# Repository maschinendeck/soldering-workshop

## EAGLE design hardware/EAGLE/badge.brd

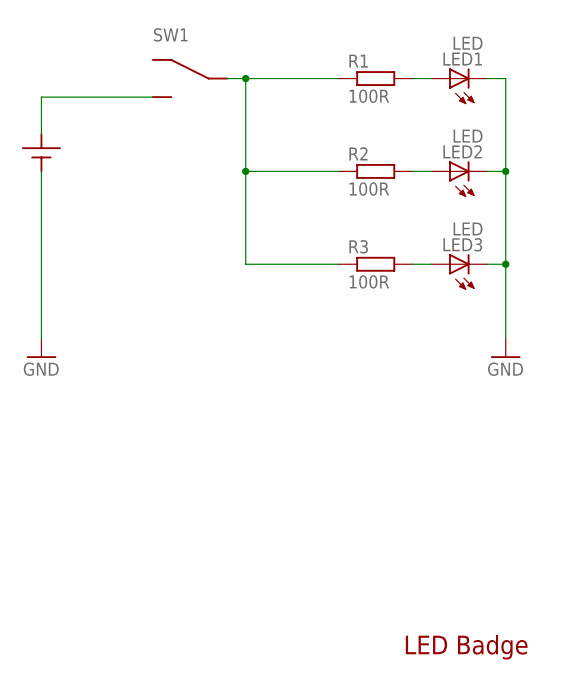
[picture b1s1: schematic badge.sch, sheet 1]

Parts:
LED1, LED2, LED3: LED; LED5MM
R1, R2, R3: 100R; 0207/10
SW1: SWITCH
X1: BATTERYHOLDER_SMD

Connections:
GND: LED1.K (C), LED2.K (C), LED3.K (C), X1.-
unnamed: LED1.A, R1.2
unnamed: R1.1, R2.1, R3.1, SW1.C
unnamed: LED2.A, R2.2
unnamed: LED3.A, R3.2
unnamed: SW1.NO, X1.+

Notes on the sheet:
LED Badge

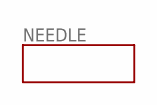
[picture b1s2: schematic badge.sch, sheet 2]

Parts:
NEEDLE: NEEDLE; NEEDLE_PAD

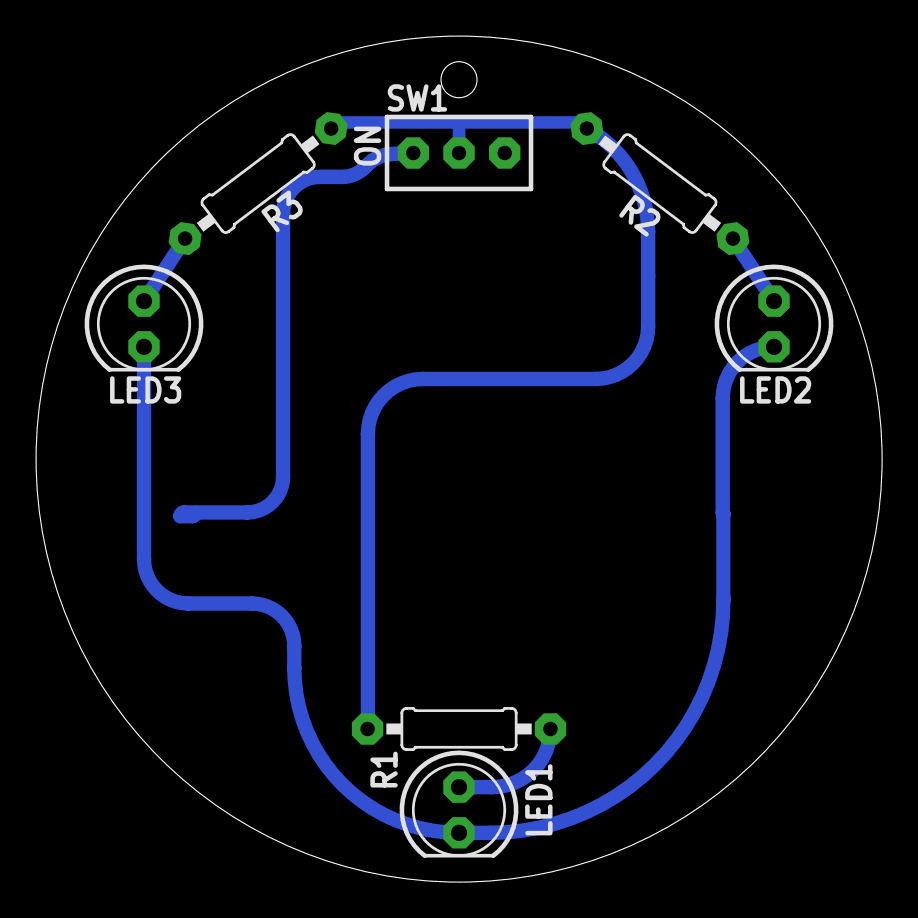
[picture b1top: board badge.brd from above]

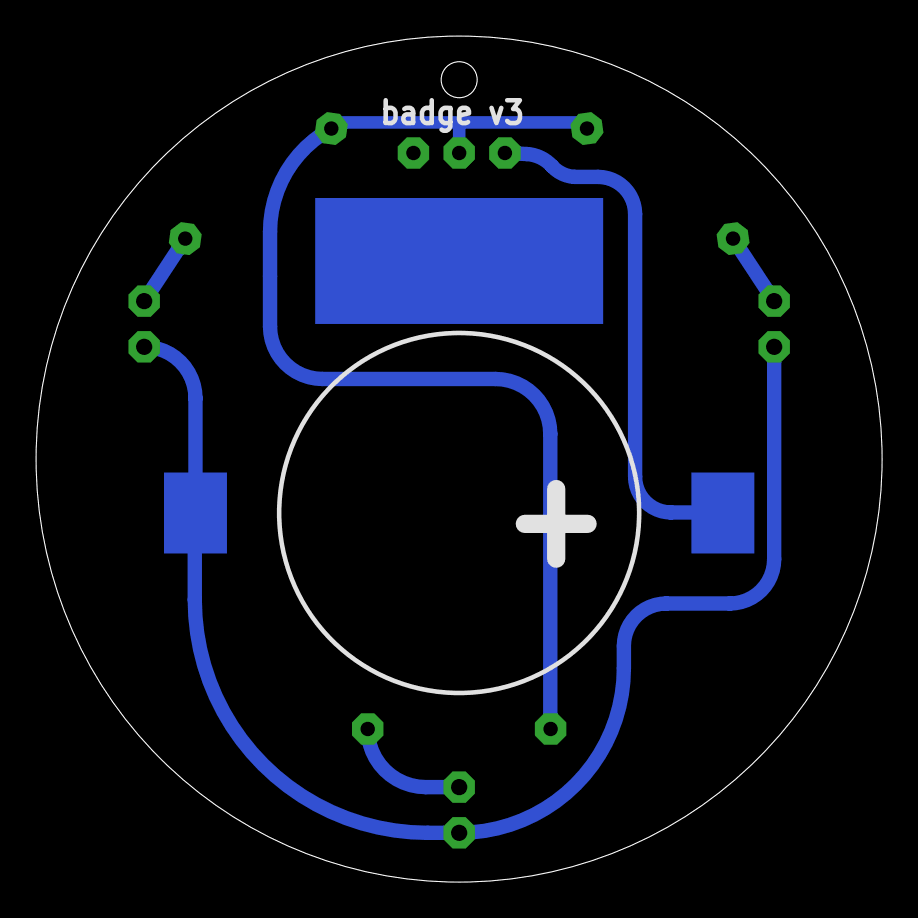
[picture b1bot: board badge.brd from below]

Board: 2 copper layers, 47.0 x 47.0 mm, 9 parts (2 on the bottom side), 6 nets.

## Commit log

2018-10-17 Reworked presentation with more detailed information
2018-10-17 Minor change (typo)
2018-10-20 Added detailed soldering steps and a useful order to assemble the parts
2018-10-28 Added assembly images
2018-10-28 Fixed wrong quotes being used in frame "zum schluss"
2018-10-28 Changed frames in the presentation
    Added images explaining the assembly of the badge
    Added a thank you page at the end
2018-10-28 Changed led polarity picture from pen anotations to digital anotations - to give it a cleaner look
2018-11-02 Fixed a few typos, added table of contents
2018-11-12 Added Klaus to author list
2019-05-30 little cleanup, minor changes
2019-05-30 added hardware
2019-05-30 added final picture
2019-05-30 fixed markdown for image
2019-11-05 removed unnecessary slides and did a bit of cleanup
2019-11-07 fixed links slide, added github qr
2019-11-10 combined explanation with pictures, removed some unnecessary stuff
2019-11-10 added synctex file to gitignore
2019-11-10 changed resistor to correct value
2019-11-16 added safety google instruction to solder slide
2019-11-16 added handout for people who are faster than others
2019-12-21 new line fixes
2019-12-21 added handout
